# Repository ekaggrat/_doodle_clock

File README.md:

_doodle_clock
=============
files for the _doodle_clock #2

http://hackaday.com/2015/10/06/robot-clock-writes-time-over-and-over-and-over/

http://www.ekaggrat.net/index.php?/lab/doodle-clock2/

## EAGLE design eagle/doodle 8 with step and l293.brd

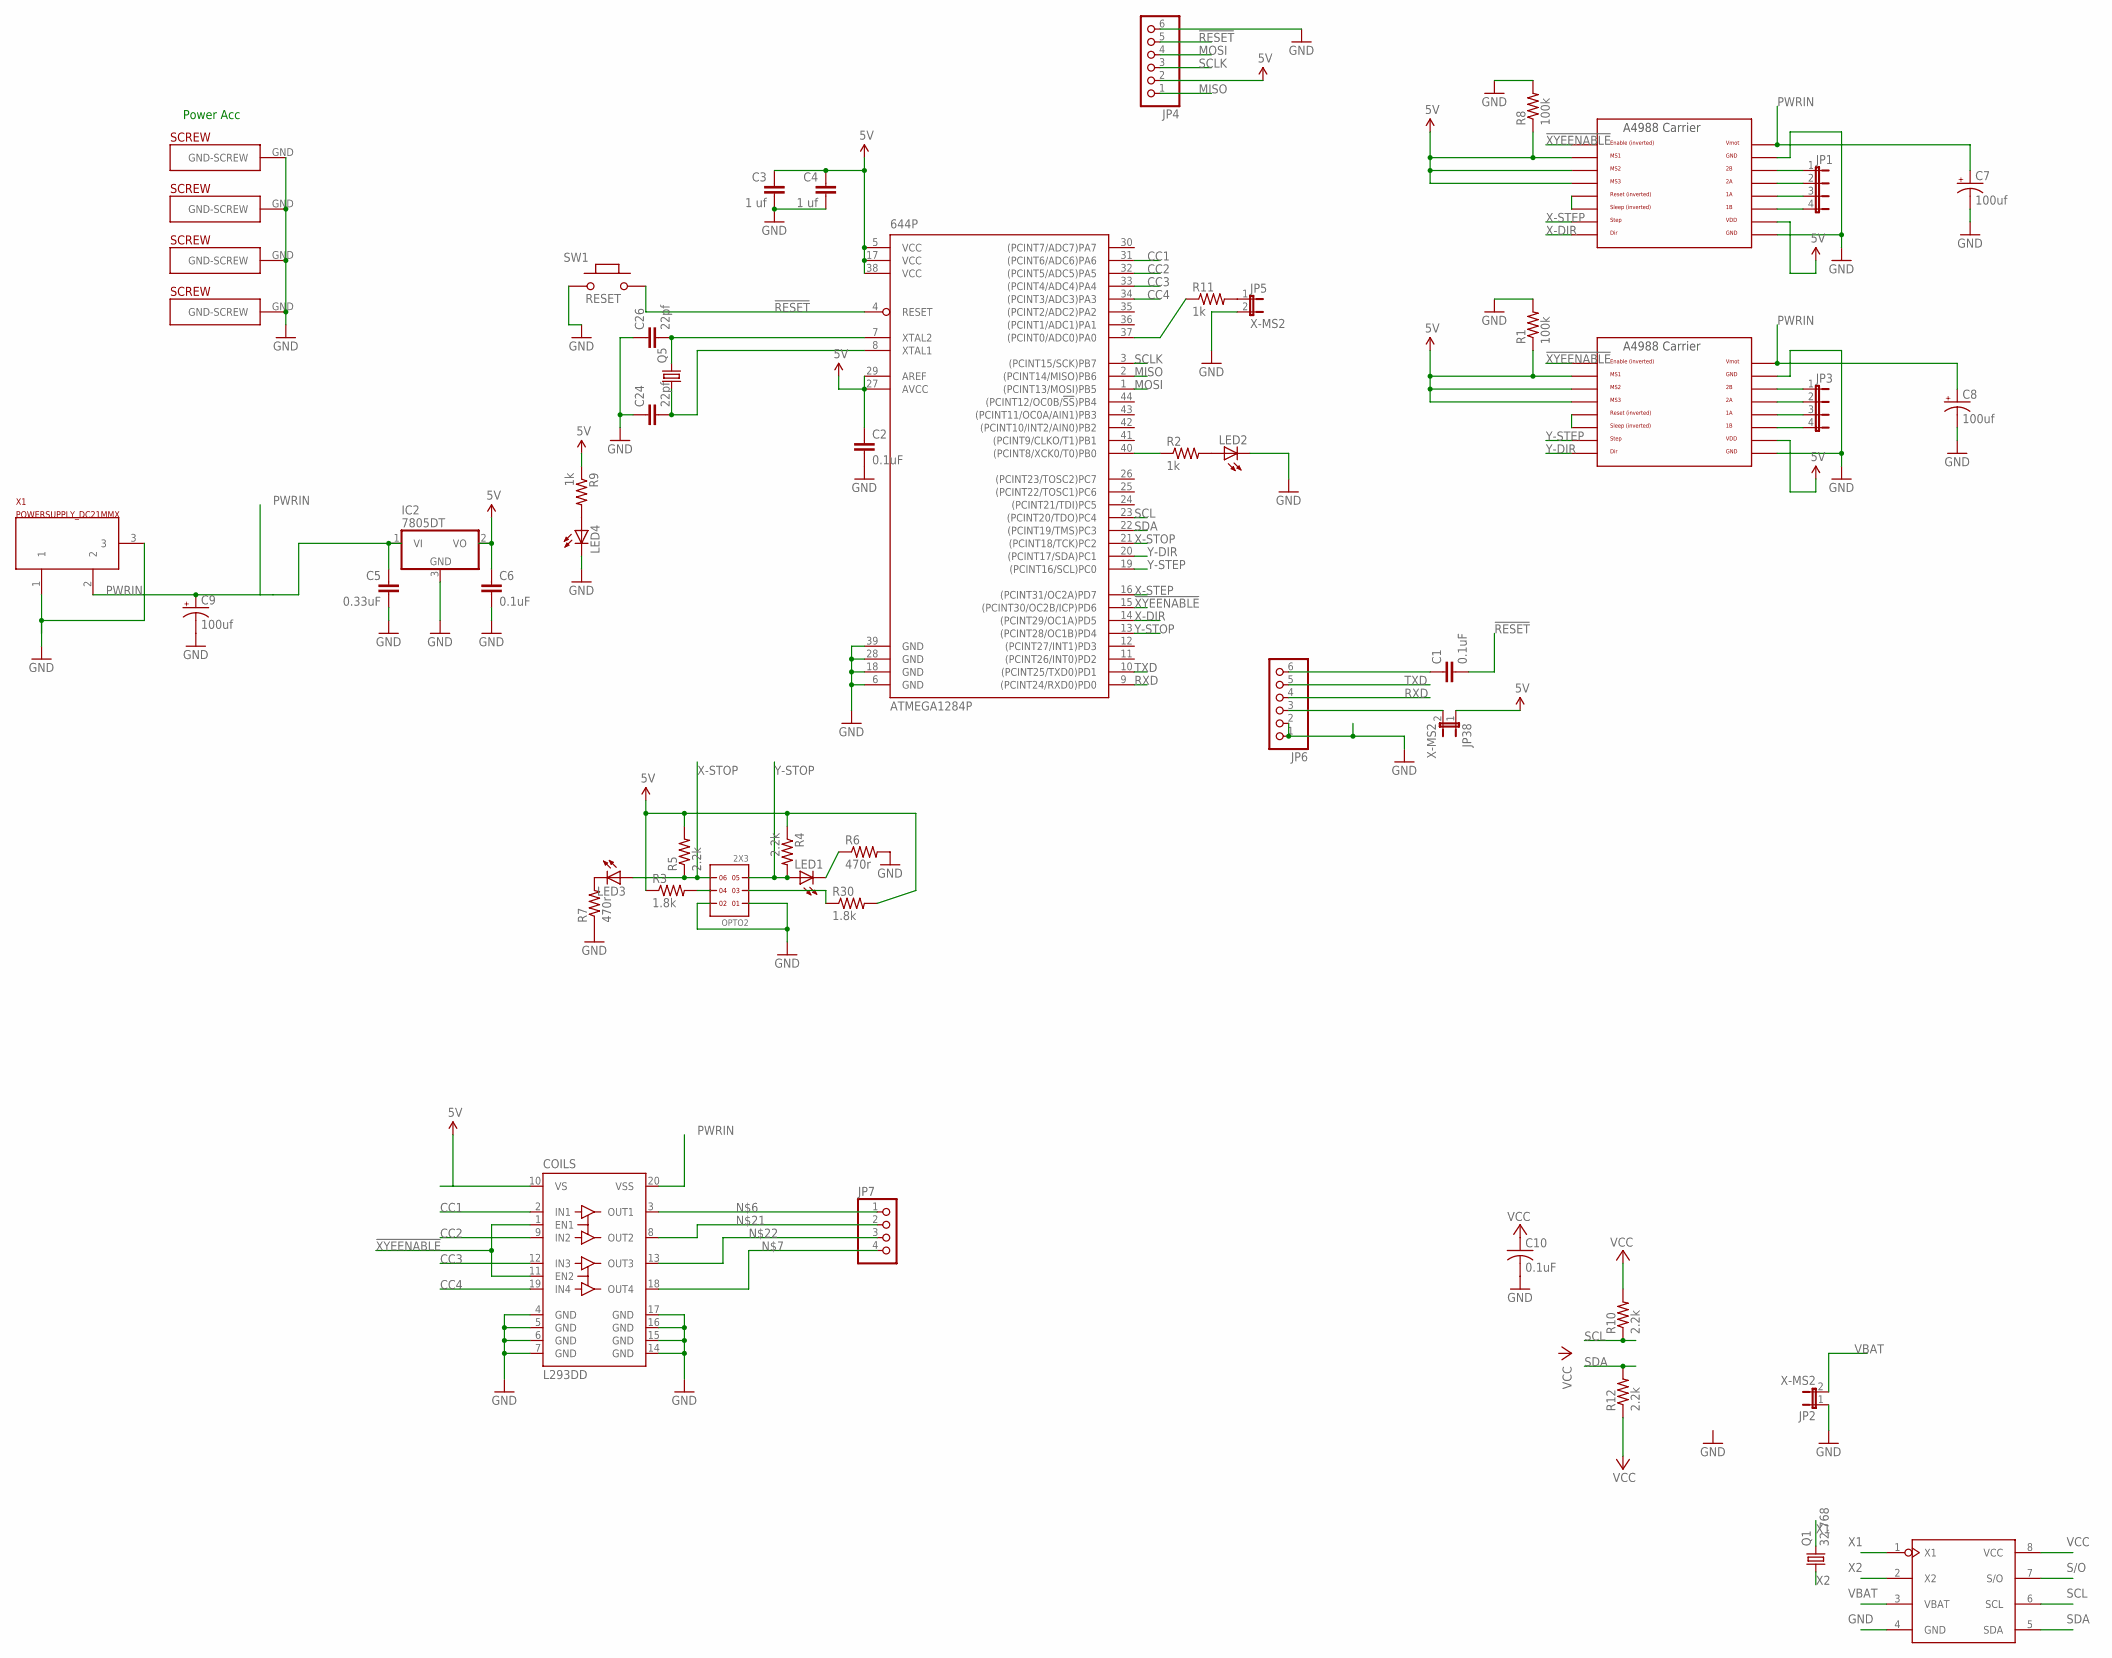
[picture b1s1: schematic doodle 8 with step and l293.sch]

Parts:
644P: ATMEGA1284P; TQFP44
C1, C2: 0.1uF; 0805
C3, C4: 1 uf; 0805
C5: 0.33uF; CAP-PTH-SMALL2
C6: 0.1uF; CAP-PTH-SMALL2
C7, C8, C9: 100uf; CPOL-RADIAL-100UF-25V
C10: 0.1uF; C0805
C24, C26: 22pf; 0805
COILS: L293DD; SO20
DS1307: DS1307; SO08
IC2: 7805DT; TO252
JP1, JP3: JP4E; JP4
JP2, JP5, JP38: X-MS2; 1X02
JP4: PINHD-1X6/90; 1X06/90
JP6: PINHD-1X6; 1X06
JP7: PINHD-1X04_2.54; 1X04
LED1, LED2, LED3, LED4: LEDCHIPLED_0805; CHIPLED_0805
OPTO2: 2X3
Q1: 32.768; TC38H
Q5: CRYSTALHC49S; HC49/S
R1, R8: 100k; R0805
R2, R9, R11: 1k; R0805
R3: 1.8k; R0805
R4, R5, R10, R12: 2.2k; R0805
R6, R7: 470r; R0805
R30: 1.8k; R0603
SW1: RESET; 157SW
U$1, U$7: A4988BREAKOUT
U$14, U$17, U$18, U$38: PLATED-SCREW; PLATEDSCREW
X1: POWERSUPPLY_DC21MMX; POWERSUPPLY_DC-21MM

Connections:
5V: 644P.5 (VCC), 644P.17 (VCC), 644P.27 (AVCC), 644P.29 (AREF), 644P.38 (VCC), C2.1, C3.1, C4.1, C6.1, COILS.10 (VS), IC2.2 (VO), JP4.2, JP38.1, R1.1, R3.1, R4.1, R5.2, R8.1, R9.1, R30.2, U$1.MS1, U$1.MS2, U$1.MS3, U$1.VDD, U$7.MS1, U$7.MS2, U$7.MS3, U$7.VDD
!RESET: 644P.4 (RESET), C1.2, JP4.5, SW1.2
!XYEENABLE: 644P.15 ((PCINT30/OC2B/ICP)PD6), COILS.1 (EN1), COILS.11 (EN2), U$1.EN, U$7.EN
CC1: 644P.31 ((PCINT6/ADC6)PA6), COILS.2 (IN1)
CC2: 644P.32 ((PCINT5/ADC5)PA5), COILS.9 (IN2)
CC3: 644P.33 ((PCINT4/ADC4)PA4), COILS.12 (IN3)
CC4: 644P.34 ((PCINT3/ADC3)PA3), COILS.19 (IN4)
GND: 644P.6 (GND), 644P.18 (GND), 644P.28 (GND), 644P.39 (GND), C2.2, C3.2, C4.2, C5.2, C6.2, C7.2 (-), C8.2 (-), C9.2 (-), C10.2, C24.1, C26.1, COILS.4 (GND), COILS.5 (GND), COILS.6 (GND), COILS.7 (GND), COILS.14 (GND), COILS.15 (GND), COILS.16 (GND), COILS.17 (GND), DS1307.4 (GND), IC2.3 (GND), JP2.1, JP4.6, JP5.2, JP6.1, JP6.2, LED2.C, LED4.C, OPTO2.1, OPTO2.2, R1.2, R6.2, R7.1, R8.2, SW1.1, U$1.GND, U$1.GND@0 (GND), U$7.GND, U$7.GND@0 (GND), U$14.GND, U$17.GND, U$18.GND, U$38.GND, X1.1, X1.3
MISO: 644P.2 ((PCINT14/MISO)PB6), JP4.1
MOSI: 644P.1 ((PCINT13/MOSI)PB5), JP4.4
unnamed: U$1.RST, U$1.SLP (SLEEP)
unnamed: JP3.1, U$1.2B
unnamed: JP3.2, U$1.2A
unnamed: JP3.3, U$1.1A
unnamed: JP3.4, U$1.1B
unnamed: COILS.3 (OUT1), JP7.1
unnamed: COILS.18 (OUT4), JP7.4
unnamed: OPTO2.4, R3.2
unnamed: LED2.A, R2.2
unnamed: 644P.40 ((PCINT8/XCK0/T0)PB0), R2.1
unnamed: LED1.C, R6.1
unnamed: LED3.C, R7.2
unnamed: OPTO2.3, R30.1
unnamed: JP1.1, U$7.2B
unnamed: JP1.2, U$7.2A
unnamed: JP1.3, U$7.1A
unnamed: JP1.4, U$7.1B
unnamed: 644P.37 ((PCINT0/ADC0)PA0), R11.1
unnamed: LED4.A, R9.2
unnamed: JP5.1, R11.2
unnamed: COILS.8 (OUT2), JP7.2
unnamed: COILS.13 (OUT3), JP7.3
unnamed: U$7.RST, U$7.SLP (SLEEP)
unnamed: C1.1, JP6.6
unnamed: JP6.3, JP38.2
unnamed: 644P.7 (XTAL2), C26.2, Q5.2
unnamed: 644P.8 (XTAL1), C24.2, Q5.1
PWRIN: C5.1, C7.1 (+), C8.1 (+), C9.1 (+), COILS.20 (VSS), IC2.1 (VI), U$1.VMOT, U$7.VMOT, X1.2
RXD: 644P.9 ((PCINT24/RXD0)PD0), JP6.4
S/O: DS1307.7 (S/O)
SCL: 644P.23 ((PCINT20/TDO)PC4), DS1307.6 (SCL), R10.1
SCLK: 644P.3 ((PCINT15/SCK)PB7), JP4.3
SDA: 644P.22 ((PCINT19/TMS)PC3), DS1307.5 (SDA), R12.2
TXD: 644P.10 ((PCINT25/TXD0)PD1), JP6.5
VBAT: DS1307.3 (VBAT), JP2.2
VCC: C10.1, DS1307.8 (VCC), R10.2, R12.1
X1: DS1307.1 (X1), Q1.2
X2: DS1307.2 (X2), Q1.1
X-DIR: 644P.14 ((PCINT29/OC1A)PD5), U$7.DIR
X-STEP: 644P.16 ((PCINT31/OC2A)PD7), U$7.STEP
X-STOP: 644P.21 ((PCINT18/TCK)PC2), LED3.A, OPTO2.6, R5.1
Y-DIR: 644P.20 ((PCINT17/SDA)PC1), U$1.DIR
Y-STEP: 644P.19 ((PCINT16/SCL)PC0), U$1.STEP
Y-STOP: 644P.13 ((PCINT28/OC1B)PD4), LED1.A, OPTO2.5, R4.2

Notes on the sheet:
Power Acc

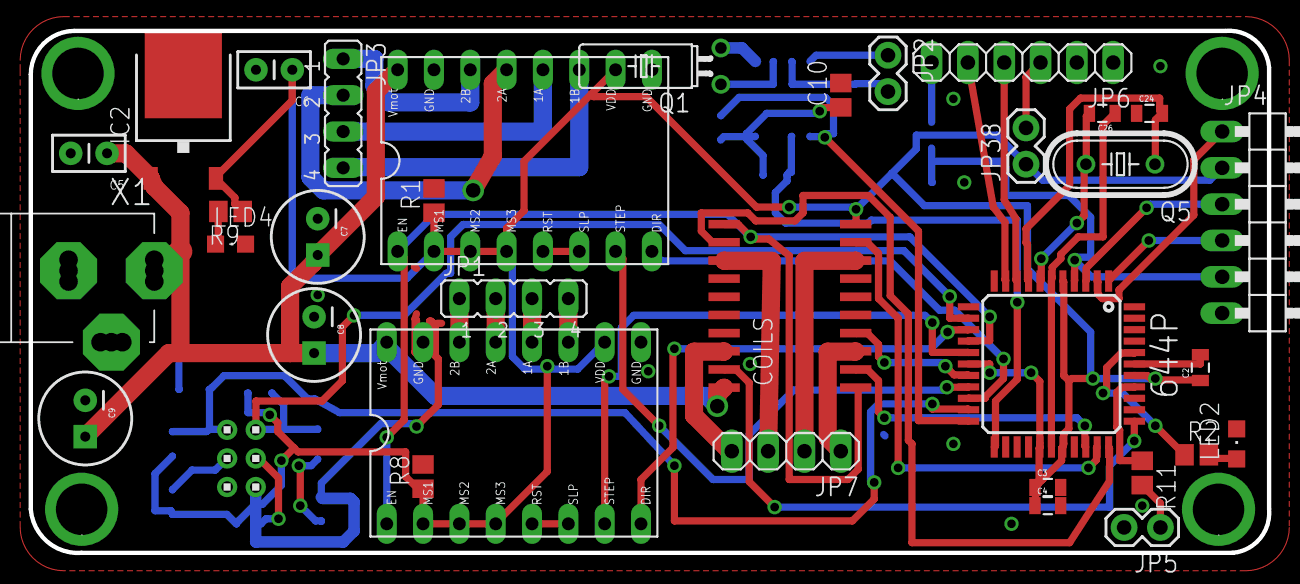
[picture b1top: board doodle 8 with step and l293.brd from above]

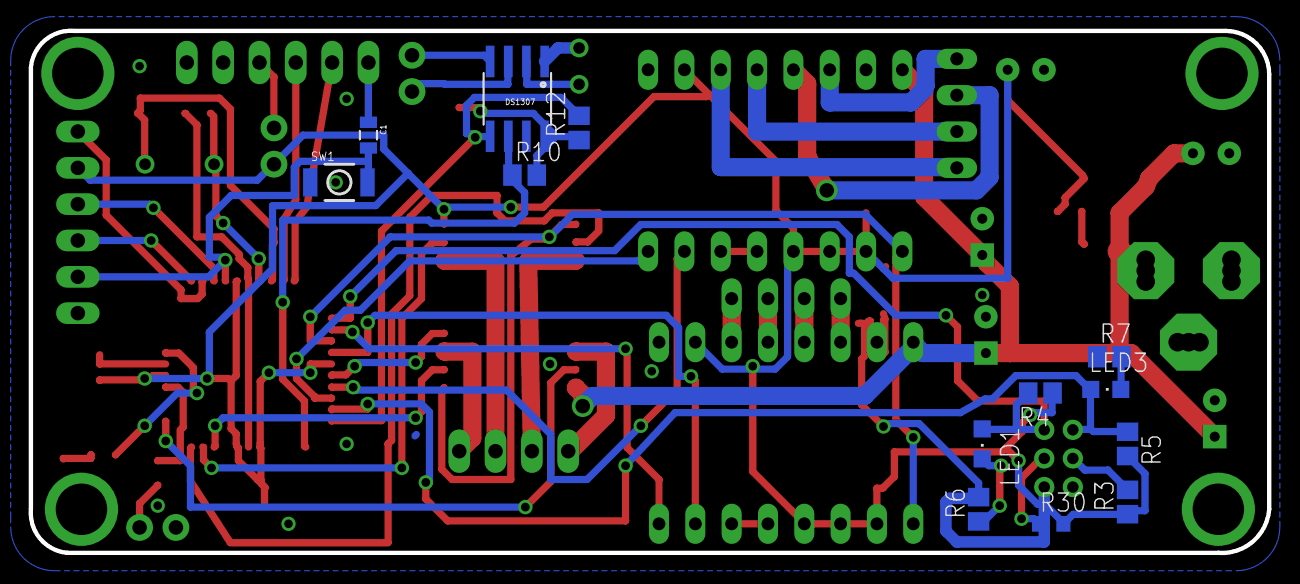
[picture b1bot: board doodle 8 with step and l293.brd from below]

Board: 2 copper layers, 86.6 x 36.5 mm, 52 parts (13 on the bottom side), 53 nets.

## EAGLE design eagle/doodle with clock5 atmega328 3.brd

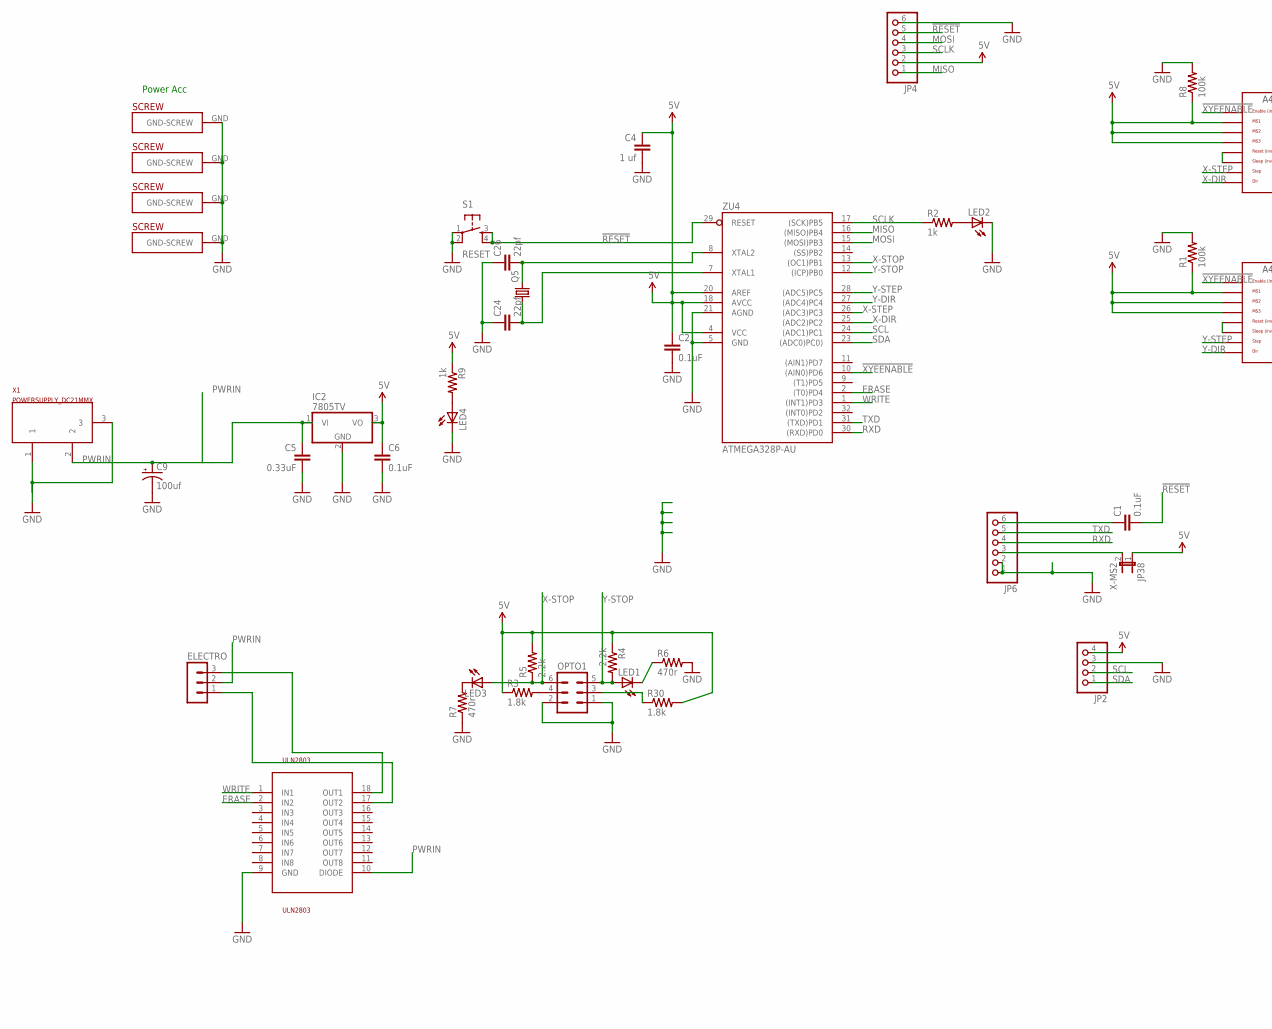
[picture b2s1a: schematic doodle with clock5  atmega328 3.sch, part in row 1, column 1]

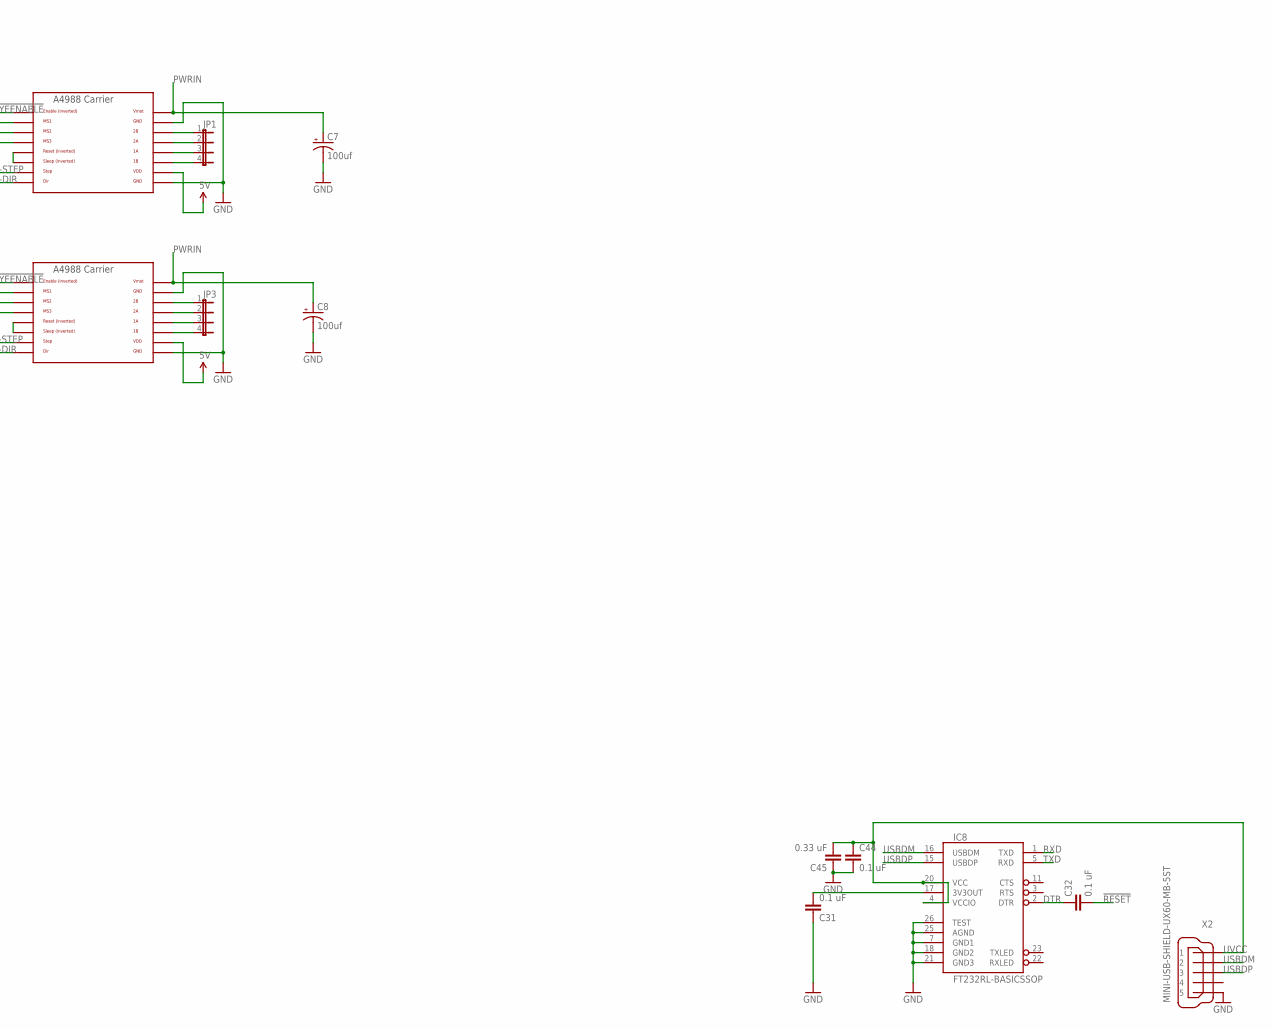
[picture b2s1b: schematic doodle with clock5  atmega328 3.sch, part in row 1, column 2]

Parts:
C1, C2: 0.1uF; 0805
C4: 1 uf; 0805
C5: 0.33uF; CAP-PTH-SMALL2
C6: 0.1uF; CAP-PTH-SMALL2
C7, C8, C9: 100uf; CPOL-RADIAL-100UF-25V
C24, C26: 22pf; 0805
C31, C32, C44: 0.1 uF; C1206
C45: 0.33 uF; C1206
ELECTRO: MA03-1
IC2: 7805TV; TO220V
IC8: FT232RL-BASICSSOP; SSOP28DB
JP1, JP3: JP4E; JP4
JP2: PINHD-1X4; 1X04
JP4: PINHD-1X6/90; 1X06/90
JP6: PINHD-1X6; 1X06
JP38: X-MS2; 1X02
LED1, LED2, LED3, LED4: LEDCHIPLED_0805; CHIPLED_0805
OPTO1: MA03-2
Q5: CRYSTALHC49S; HC49/S
R1, R8: 100k; 0207/7
R2, R9: 1k; R0805
R3: 1.8k; R0805
R4, R5: 2.2k; R0805
R6, R7: 470r; R0805
R30: 1.8k; R0603
S1: RESET; TACTILE-PTH
U$1, U$7: A4988BREAKOUT
U$14, U$17, U$18, U$38: PLATED-SCREW; PLATEDSCREW
ULN2803: ULN2803; SO18L
X1: POWERSUPPLY_DC21MMX; POWERSUPPLY_DC-21MM
X2: MINI-USB-SHIELD-UX60-MB-5ST; UX60-MB-5ST
ZU4: ATMEGA328P-AU; TQFP32-08

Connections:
5V: C2.1, C4.1, C6.1, IC2.3 (VO), JP2.4, JP4.2, JP38.1, R1.1, R3.1, R4.1, R5.2, R8.1, R9.1, R30.2, U$1.MS1, U$1.MS2, U$1.MS3, U$1.VDD, U$7.MS1, U$7.MS2, U$7.MS3, U$7.VDD, ZU4.4 (VCC), ZU4.18 (AVCC), ZU4.20 (AREF)
!RESET: C1.2, C32.2, JP4.5, S1.3, S1.4, ZU4.29 (RESET)
!XYEENABLE: U$1.EN, U$7.EN, ZU4.10 ((AIN0)PD6)
DTR: C32.1, IC8.2 (DTR)
ERASE: ULN2803.2 (IN2), ZU4.2 ((T0)PD4)
GND: C2.2, C4.2, C5.2, C6.2, C7.2 (-), C8.2 (-), C9.2 (-), C24.1, C26.1, C31.1, C44.2, C45.1, IC2.2 (GND), IC8.7 (GND1), IC8.18 (GND2), IC8.21 (GND3), IC8.25 (AGND), IC8.26 (TEST), JP2.3, JP4.6, JP6.1, JP6.2, LED2.C, LED4.C, OPTO1.1, OPTO1.2, R1.2, R6.2, R7.1, R8.2, S1.1, S1.2, U$1.GND, U$1.GND@0 (GND), U$7.GND, U$7.GND@0 (GND), U$14.GND, U$17.GND, U$18.GND, U$38.GND, ULN2803.9 (GND), X1.1, X1.3, X2.5, ZU4.5 (GND), ZU4.21 (AGND)
MISO: JP4.1, ZU4.16 ((MISO)PB4)
MOSI: JP4.4, ZU4.15 ((MOSI)PB3)
unnamed: U$1.RST, U$1.SLP (SLEEP)
unnamed: JP3.1, U$1.2B
unnamed: JP3.2, U$1.2A
unnamed: JP3.3, U$1.1A
unnamed: JP3.4, U$1.1B
unnamed: ELECTRO.1, ULN2803.17 (OUT2)
unnamed: ELECTRO.3, ULN2803.18 (OUT1)
unnamed: OPTO1.4, R3.2
unnamed: LED2.A, R2.2
unnamed: LED1.C, R6.1
unnamed: LED3.C, R7.2
unnamed: OPTO1.3, R30.1
unnamed: JP1.1, U$7.2B
unnamed: JP1.2, U$7.2A
unnamed: JP1.3, U$7.1A
unnamed: JP1.4, U$7.1B
unnamed: C31.2, IC8.17 (3V3OUT)
unnamed: LED4.A, R9.2
unnamed: U$7.RST, U$7.SLP (SLEEP)
unnamed: C1.1, JP6.6
unnamed: JP6.3, JP38.2
unnamed: C26.2, Q5.2, ZU4.8 (XTAL2)
unnamed: C24.2, Q5.1, ZU4.7 (XTAL1)
PWRIN: C5.1, C7.1 (+), C8.1 (+), C9.1 (+), ELECTRO.2, IC2.1 (VI), U$1.VMOT, U$7.VMOT, ULN2803.10 (DIODE), X1.2
RXD: IC8.1 (TXD), JP6.4, ZU4.30 ((RXD)PD0)
SCL: JP2.2, ZU4.24 ((ADC1)PC1)
SCLK: JP4.3, R2.1, ZU4.17 ((SCK)PB5)
SDA: JP2.1, ZU4.23 ((ADC0)PC0))
TXD: IC8.5 (RXD), JP6.5, ZU4.31 ((TXD)PD1)
USBDM: IC8.16 (USBDM), X2.2
USBDP: IC8.15 (USBDP), X2.3
UVCC: C44.1, C45.2, IC8.4 (VCCIO), IC8.20 (VCC), X2.1
WRITE: ULN2803.1 (IN1), ZU4.1 ((INT1)PD3)
X-DIR: U$7.DIR, ZU4.25 ((ADC2)PC2)
X-STEP: U$7.STEP, ZU4.26 ((ADC3)PC3)
X-STOP: LED3.A, OPTO1.6, R5.1, ZU4.13 ((OC1)PB1)
Y-DIR: U$1.DIR, ZU4.27 ((ADC4)PC4)
Y-STEP: U$1.STEP, ZU4.28 ((ADC5)PC5)
Y-STOP: LED1.A, OPTO1.5, R4.2, ZU4.12 ((ICP)PB0)

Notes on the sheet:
Power Acc

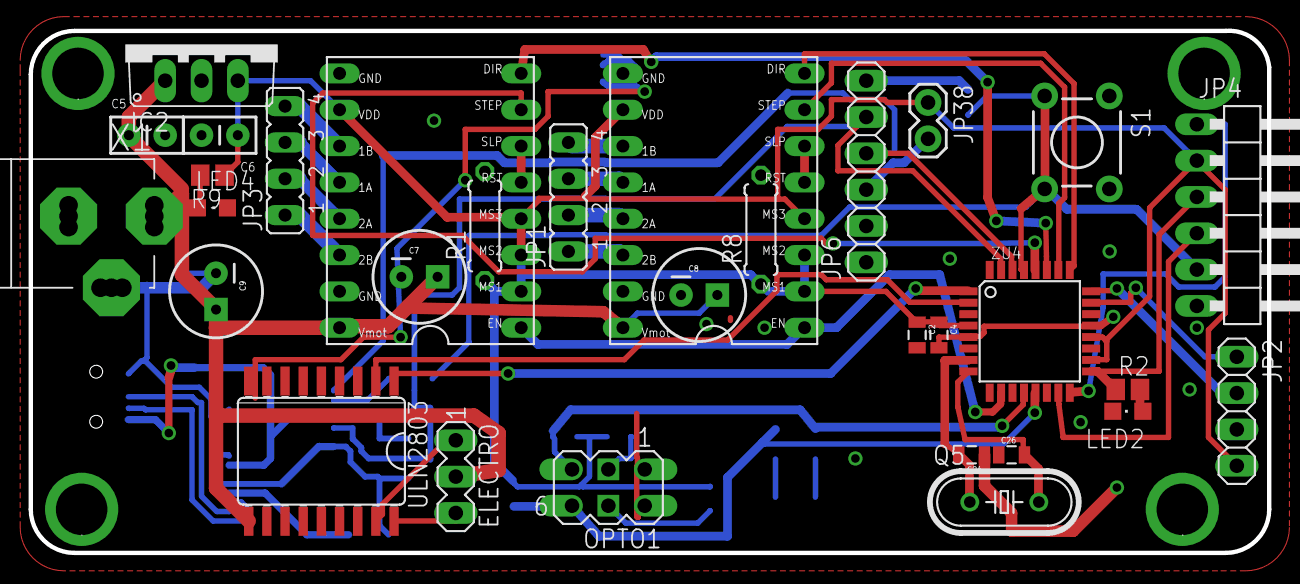
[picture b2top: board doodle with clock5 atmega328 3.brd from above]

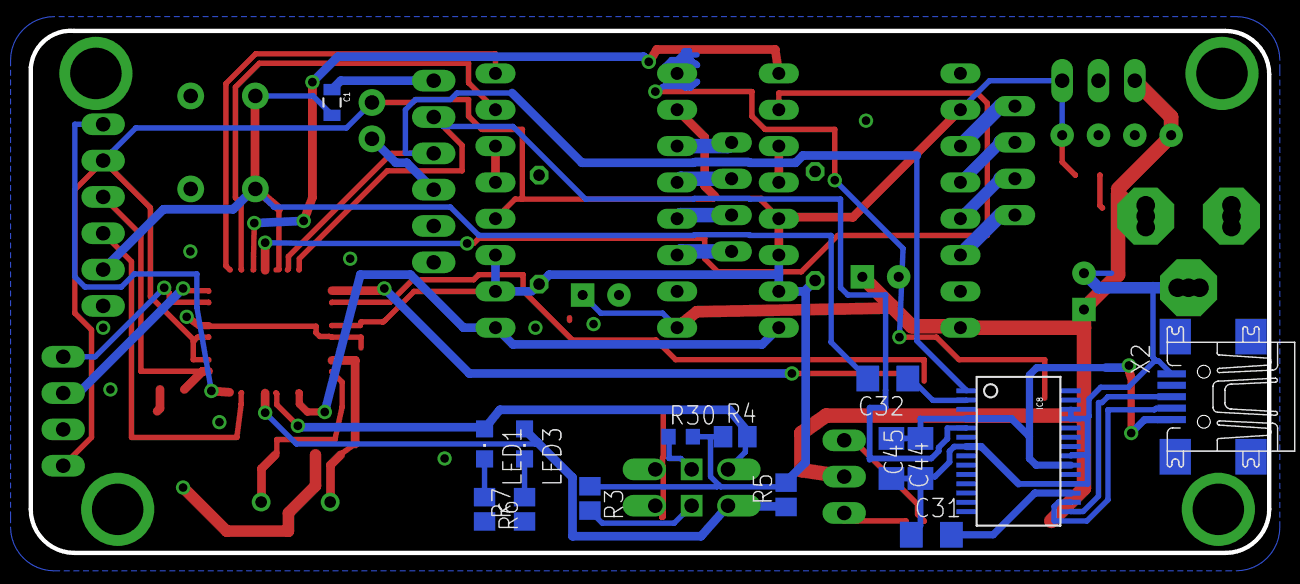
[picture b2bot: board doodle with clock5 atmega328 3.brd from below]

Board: 2 copper layers, 86.6 x 36.5 mm, 50 parts (15 on the bottom side), 47 nets.

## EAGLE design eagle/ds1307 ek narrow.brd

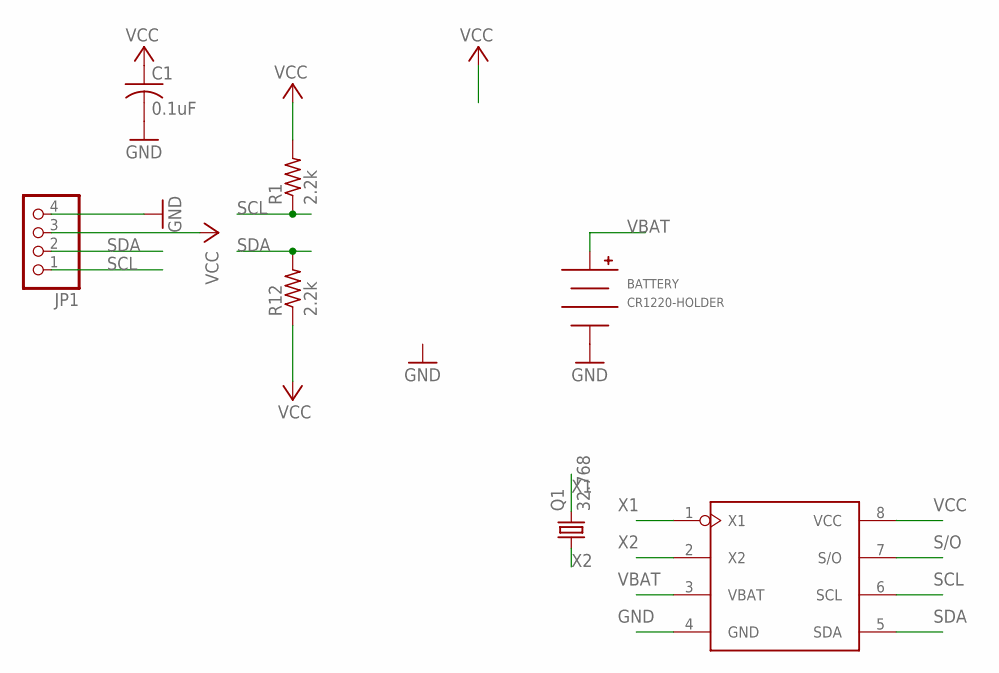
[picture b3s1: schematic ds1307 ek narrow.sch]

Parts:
BATTERY: CR1220-HOLDER; HARWIN-CR1220
C1: 0.1uF; C0805
DS1307: DS1307; SO08
JP1: PINHD-1X4; 1X04
Q1: 32.768; TC38H
R1, R12: 2.2k; R0805

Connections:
GND: BATTERY.NEG, C1.2, DS1307.4 (GND), JP1.4
S/O: DS1307.7 (S/O)
SCL: DS1307.6 (SCL), JP1.1, R1.1
SDA: DS1307.5 (SDA), JP1.2, R12.2
VBAT: BATTERY.POS, DS1307.3 (VBAT)
VCC: C1.1, DS1307.8 (VCC), JP1.3, R1.2, R12.1
X1: DS1307.1 (X1), Q1.2
X2: DS1307.2 (X2), Q1.1

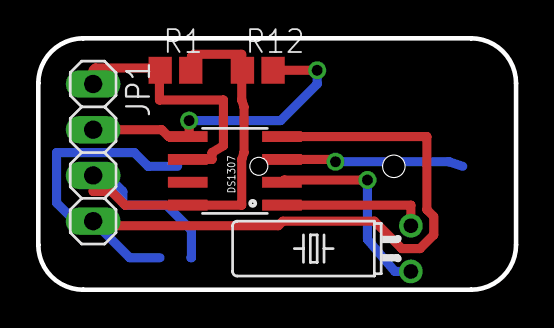
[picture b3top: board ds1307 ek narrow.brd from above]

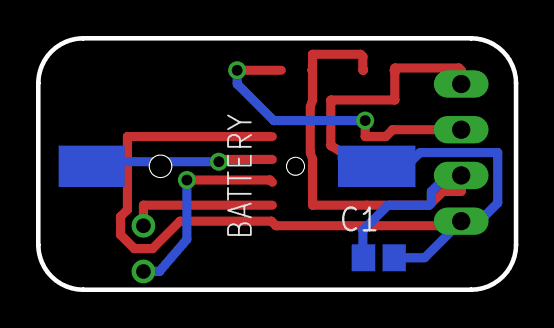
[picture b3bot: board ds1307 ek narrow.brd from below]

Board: 2 copper layers, 26.5 x 14.0 mm, 7 parts (2 on the bottom side), 7 nets.

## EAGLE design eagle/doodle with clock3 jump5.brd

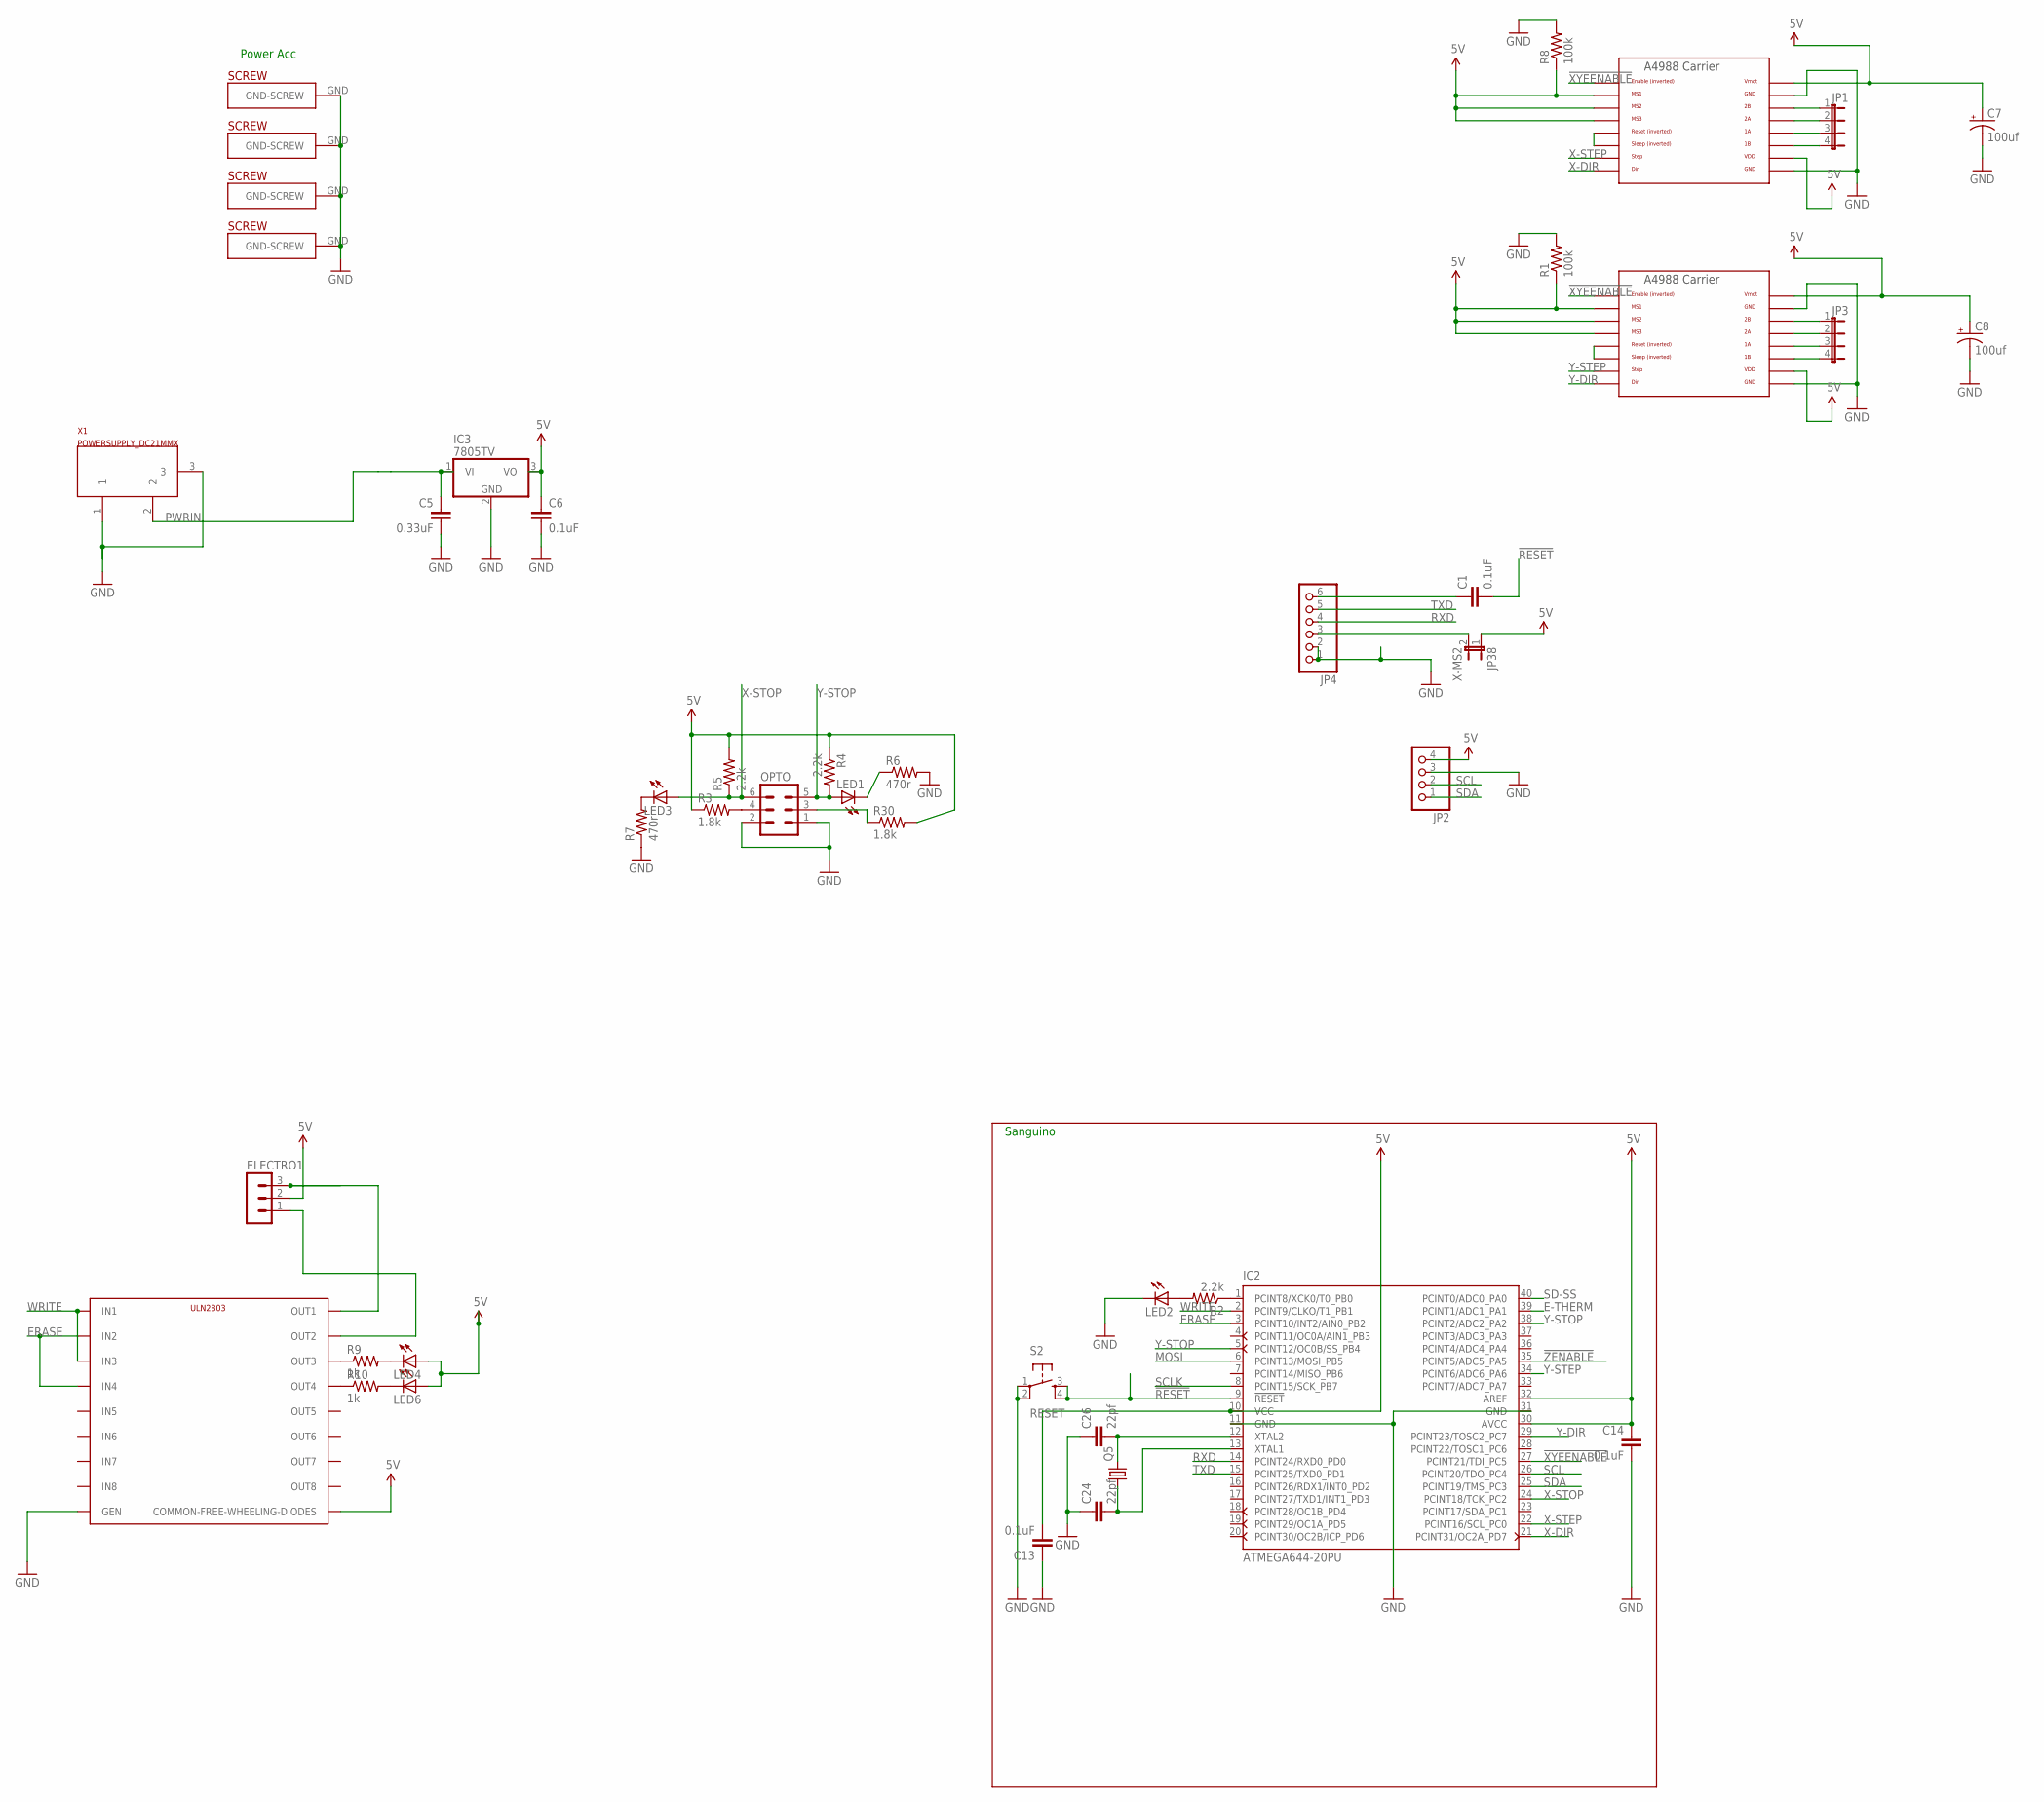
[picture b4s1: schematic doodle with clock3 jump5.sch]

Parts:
C1, C6, C13, C14: 0.1uF; CAP-PTH-SMALL2
C5: 0.33uF; CAP-PTH-SMALL2
C7, C8: 100uf; CPOL-RADIAL-100UF-25V
C24, C26: 22pf; CAP-PTH-SMALL2
ELECTRO1: MA03-1
IC2: ATMEGA644-20PU; DIL40
IC3: 7805TV; TO220V
JP1, JP3: JP4E; JP4
JP2: PINHD-1X4; 1X04
JP4: PINHD-1X6/90; 1X06/90
JP38: X-MS2; 1X02
LED1, LED2, LED3, LED4, LED6: LED3MM
OPTO: MA03-2
Q5: CRYSTALHC49S; HC49/S
R1, R8: 100k; 0207/7
R2, R4, R5: 2.2k; 0207/2V
R3, R30: 1.8k; 0207/2V
R6, R7: 470r; 0207/2V
R9, R10: 1k; 0207/2V
S2: RESET; TACTILE-PTH
U$1, U$7: A4988BREAKOUT
U$2: ULN2803; P-DIP
U$14, U$17, U$18, U$38: PLATED-SCREW; PLATEDSCREW
X1: POWERSUPPLY_DC21MMX; POWERSUPPLY_DC-21MM

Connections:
5V: C6.1, C7.1 (+), C8.1 (+), C13.2, C14.1, ELECTRO1.2, IC2.10 (VCC), IC2.30 (AVCC), IC2.32 (AREF), IC3.3 (VO), JP2.4, JP38.1, LED4.A, LED6.A, R1.1, R3.1, R4.1, R5.2, R8.1, R30.2, U$1.MS1, U$1.MS2, U$1.MS3, U$1.VDD, U$1.VMOT, U$2.COMMON-FREE-WHEELIN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, U$7.MS1, U$7.MS2, U$7.MS3, U$7.VDD, U$7.VMOT
!RESET: C1.2, IC2.9 (!RESET), S2.3, S2.4
!XYEENABLE: IC2.27 (PCINT21/TDI_PC5), U$1.EN, U$7.EN
!ZENABLE: IC2.35 (PCINT5/ADC5_PA5)
E-THERM: IC2.39 (PCINT1/ADC1_PA1)
ERASE: IC2.3 (PCINT10/INT2/AIN0_PB2), U$2.IN2, U$2.IN4
GND: C5.2, C6.2, C7.2 (-), C8.2 (-), C13.1, C14.2, C24.1, C26.1, IC2.11 (GND), IC2.31 (GND), IC3.2 (GND), JP2.3, JP4.1, JP4.2, LED2.K (C), OPTO.1, OPTO.2, R1.2, R6.2, R7.1, R8.2, S2.1, S2.2, U$1.GND, U$1.GND@0 (GND), U$2.GEN, U$7.GND, U$7.GND@0 (GND), U$14.GND, U$17.GND, U$18.GND, U$38.GND, X1.1, X1.3
MOSI: IC2.6 (PCINT13/MOSI_PB5)
unnamed: U$1.RST, U$1.SLP (SLEEP)
unnamed: JP3.1, U$1.2B
unnamed: JP3.2, U$1.2A
unnamed: JP3.3, U$1.1A
unnamed: JP3.4, U$1.1B
unnamed: IC2.1 (PCINT8/XCK0/T0_PB0), R2.1
unnamed: LED2.A, R2.2
unnamed: R9.1, U$2.OUT3
unnamed: OPTO.4, R3.2
unnamed: LED4.K (C), R9.2
unnamed: LED1.K (C), R6.1
unnamed: LED3.K (C), R7.2
unnamed: OPTO.3, R30.1
unnamed: JP1.1, U$7.2B
unnamed: JP1.2, U$7.2A
unnamed: JP1.3, U$7.1A
unnamed: JP1.4, U$7.1B
unnamed: ELECTRO1.1, U$2.OUT2
unnamed: ELECTRO1.3, U$2.OUT1
unnamed: R10.1, U$2.OUT4
unnamed: LED6.K (C), R10.2
unnamed: U$7.RST, U$7.SLP (SLEEP)
unnamed: C1.1, JP4.6
unnamed: JP4.3, JP38.2
unnamed: C26.2, IC2.12 (XTAL2), Q5.2
unnamed: C24.2, IC2.13 (XTAL1), Q5.1
PWRIN: C5.1, IC3.1 (VI), X1.2
RXD: IC2.14 (PCINT24/RXD0_PD0), JP4.4
SCL: IC2.26 (PCINT20/TDO_PC4), JP2.2
SCLK: IC2.8 (PCINT15/SCK_PB7)
SD-SS: IC2.40 (PCINT0/ADC0_PA0)
SDA: IC2.25 (PCINT19/TMS_PC3), JP2.1
TXD: IC2.15 (PCINT25/TXD0_PD1), JP4.5
WRITE: IC2.2 (PCINT9/CLKO/T1_PB1), U$2.IN1, U$2.IN3
X-DIR: IC2.21 (PCINT31/OC2A_PD7), U$7.DIR
X-STEP: IC2.22 (PCINT16/SCL_PC0), U$7.STEP
X-STOP: IC2.24 (PCINT18/TCK_PC2), LED3.A, OPTO.6, R5.1
Y-DIR: IC2.29 (PCINT23/TOSC2_PC7), U$1.DIR
Y-STEP: IC2.34 (PCINT6/ADC6_PA6), U$1.STEP
Y-STOP: IC2.5 (PCINT12/OC0B/SS_PB4), IC2.38 (PCINT2/ADC2_PA2), LED1.A, OPTO.5, R4.2

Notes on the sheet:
Power Acc
Sanguino

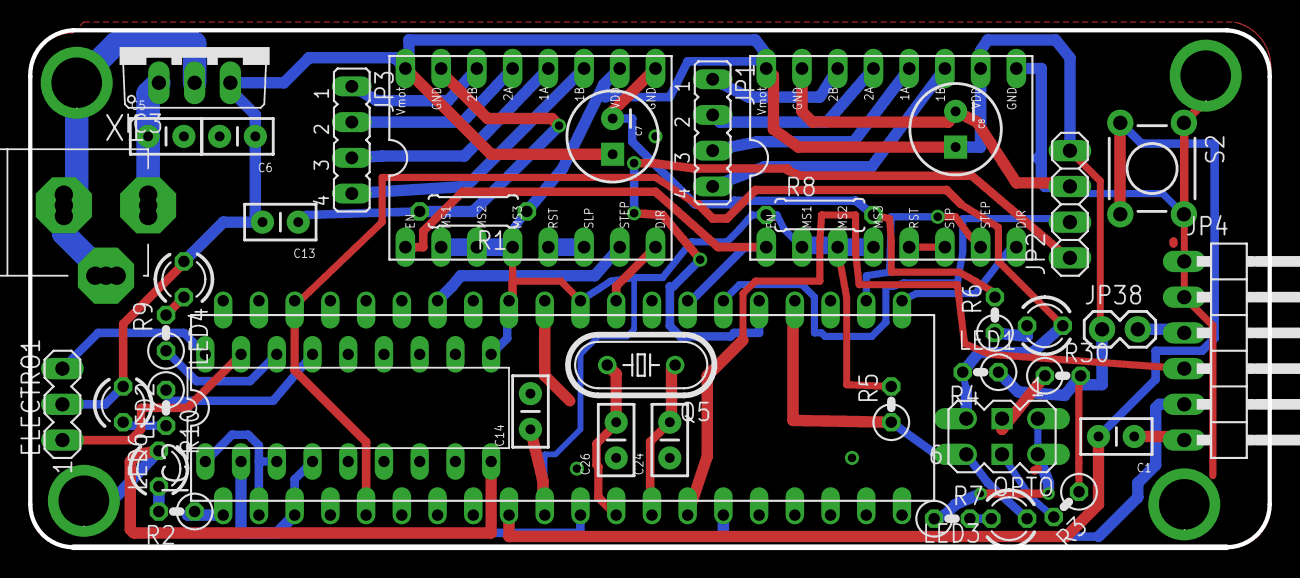
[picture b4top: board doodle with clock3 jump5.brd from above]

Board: 2 copper layers, 88.1 x 36.8 mm, 44 parts (0 on the bottom side), 43 nets.
